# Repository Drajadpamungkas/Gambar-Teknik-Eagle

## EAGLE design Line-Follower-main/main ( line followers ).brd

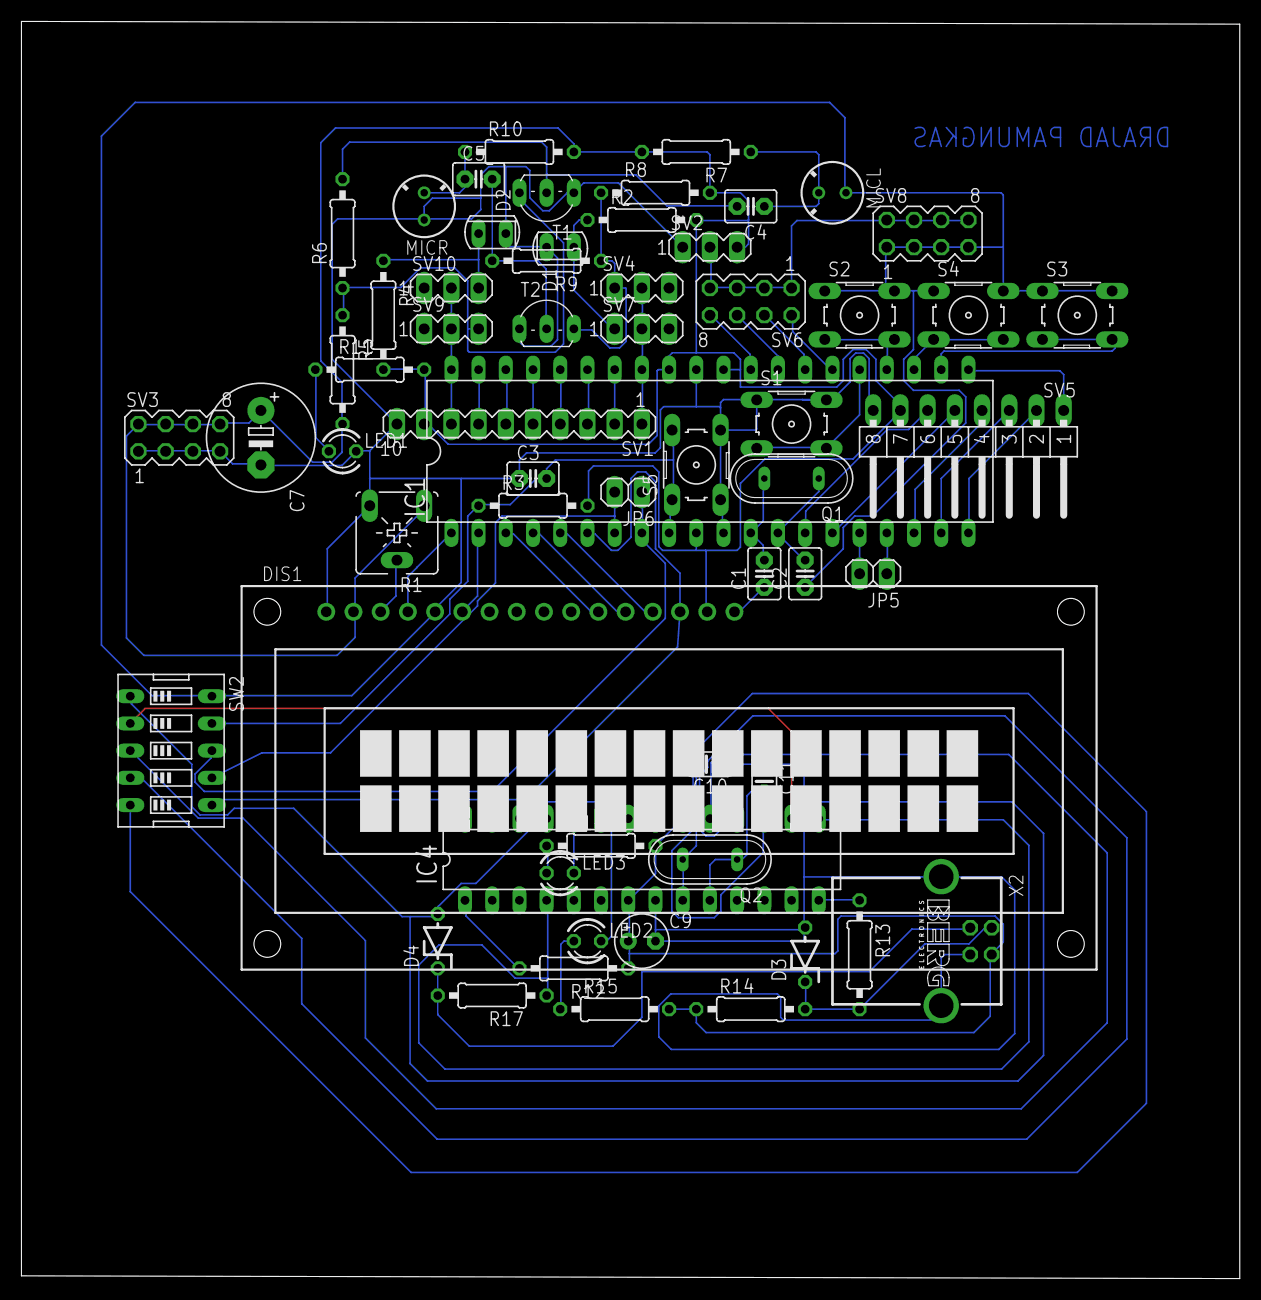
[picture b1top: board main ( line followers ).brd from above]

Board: 2 copper layers, 113.7 x 117.3 mm, 61 parts (0 on the bottom side), 65 nets.

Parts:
C1, C2: 22p; C2.5-3
C3: 10nF; C2.5-3
C4, C5: 100nF; C2.5-3
C7: 1000uF/16V; E5-10,5
C9: 10uF/16V; E2,5-5
C10, C11: 22pF; C025-024X044
D1, D2: SFH225
D3, D4: DZ3,6V; ZDIO-5
DIS1: TUXGR_16X2_R2
IC1: MEGA16-P; DIL40
IC4: MEGA8-P; DIL28-3
JP5, JP6: 1X02
LED1: merah; LED3MM
LED2: Merah; LED3MM
LED3: hijau; LED3MM
MICL: MC; F6050AP
MICR: MC; F6050AP
Q1: 8MHz; QS
Q2: 12MHz; QS
R1: 20K; CA6V
R2, R4: 56K; 0207/10
R3, R5, R7, R8, R10, R12: 10K; 0207/10
R6, R9: 100K; 0207/10
R11, R15, R16: 330; 0207/10
R13, R17: 68; 0207/10
R14: 2K2; 0207/10
S1, S2, S3, S4, S5: B3F-10XX
SV1: MA10-1
SV2, SV4, SV7, SV9, SV10: MA03-1
SV3, SV6, SV8: MA04-2
SV5: MA08-1W
SW2: EDG-05
T1, T2: TO92-EBC
X2: PN61729-S

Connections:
DGND: C9.-, C10.1, C11.1, D3.A, D4.A, IC4.8, IC4.22, SW2.1, X2.4, X2.S1, X2.S2
GND: C1.1, C2.1, C3.1, C7.-, D1.K, D2.K, DIS1.1, DIS1.5, DIS1.16, IC1.11, IC1.31, LED1.K, MICL.1, MICR.1, R1.E, S1.1, S1.2, S2.1, S2.2, S3.1, S3.2, S4.1, S4.2, S5.3, S5.4, SV1.10, SV2.1, SV3.1, SV3.3, SV3.5, SV3.7, SV5.8, SV8.1, SV8.3, SV8.5, SV8.7, SW2.10, T1.E, T2.E
MISO: IC1.7, JP6.2, SW2.7
MOSI: DIS1.14, IC1.6, SW2.6
unnamed: IC1.33, SV1.1, SV4.2, SV7.2
unnamed: IC1.34, SV1.2
unnamed: IC1.35, SV1.3
unnamed: IC1.36, SV1.4
unnamed: IC1.37, SV1.5
unnamed: IC1.38, SV1.6
unnamed: IC1.39, SV1.7
unnamed: D2.A, R4.1, SV10.3
unnamed: IC1.24, S2.3, S2.4
unnamed: DIS1.13, IC1.5
unnamed: DIS1.12, IC1.4
unnamed: DIS1.11, IC1.3
unnamed: DIS1.6, IC1.2
unnamed: R5.1, R6.1, SV9.3, T1.C
unnamed: DIS1.3, R1.S
unnamed: C1.2, IC1.12, Q1.2
unnamed: C2.2, IC1.13, Q1.1
unnamed: DIS1.4, IC1.1
unnamed: D1.A, R2.1, SV7.1
unnamed: IC1.23, S4.3, S4.4
unnamed: IC1.40, SV1.8, SV9.2, SV10.2
unnamed: C4.2, R6.2, T1.B
unnamed: C4.1, MICL.2, R7.1
unnamed: R8.1, R9.1, SV4.1, T2.C
unnamed: C5.2, R9.2, T2.B
unnamed: C5.1, MICR.2, R10.1
unnamed: IC1.22, S3.3, S3.4
unnamed: IC1.25, S1.3, S1.4
unnamed: IC1.21, SV5.1
unnamed: IC1.20, SV5.2
unnamed: IC1.19, SV5.3
unnamed: IC1.18, SV5.4
unnamed: IC1.15, SV5.5
unnamed: IC1.14, SV5.6
unnamed: IC1.16, JP5.2
unnamed: IC1.17, JP5.1
unnamed: LED1.A, R11.1
unnamed: IC4.1, R12.2
unnamed: IC1.26, SV6.2
unnamed: IC1.27, SV6.4
unnamed: IC1.28, SV6.6
unnamed: IC1.29, SV6.8
unnamed: C10.2, IC4.9, Q2.2
unnamed: C11.2, IC4.10, Q2.1
unnamed: IC4.14, R13.1
unnamed: LED2.A, R15.1
unnamed: LED3.A, R16.1
unnamed: IC4.23, LED2.K
unnamed: IC4.24, LED3.K
unnamed: D4.C, R17.2, X2.3
unnamed: IC4.4, IC4.15, R17.1
unnamed: D3.C, R13.2, R14.2, X2.2
unnamed: IC4.17, SW2.5
unnamed: IC4.18, SW2.4
unnamed: IC4.19, SW2.3
unnamed: IC4.16, SW2.2
RESET: C3.2, IC1.9, R3.1, S5.1, S5.2, SW2.9
SCK: IC1.8, JP6.1, SW2.8
VCC: C7.+, DIS1.2, DIS1.15, IC1.10, IC1.30, IC1.32, R1.A, R2.2, R3.2, R4.2, R5.2, R7.2, R8.2, R10.2, R11.2, SV1.9, SV2.3, SV3.2, SV3.4, SV3.6, SV3.8, SV5.7
VDD: SV2.2, SV6.1, SV6.3, SV6.5, SV6.7, SV8.2, SV8.4, SV8.6, SV8.8
VPP: C9.+, IC4.7, IC4.20, R12.1, R14.1, R15.2, R16.2, X2.1

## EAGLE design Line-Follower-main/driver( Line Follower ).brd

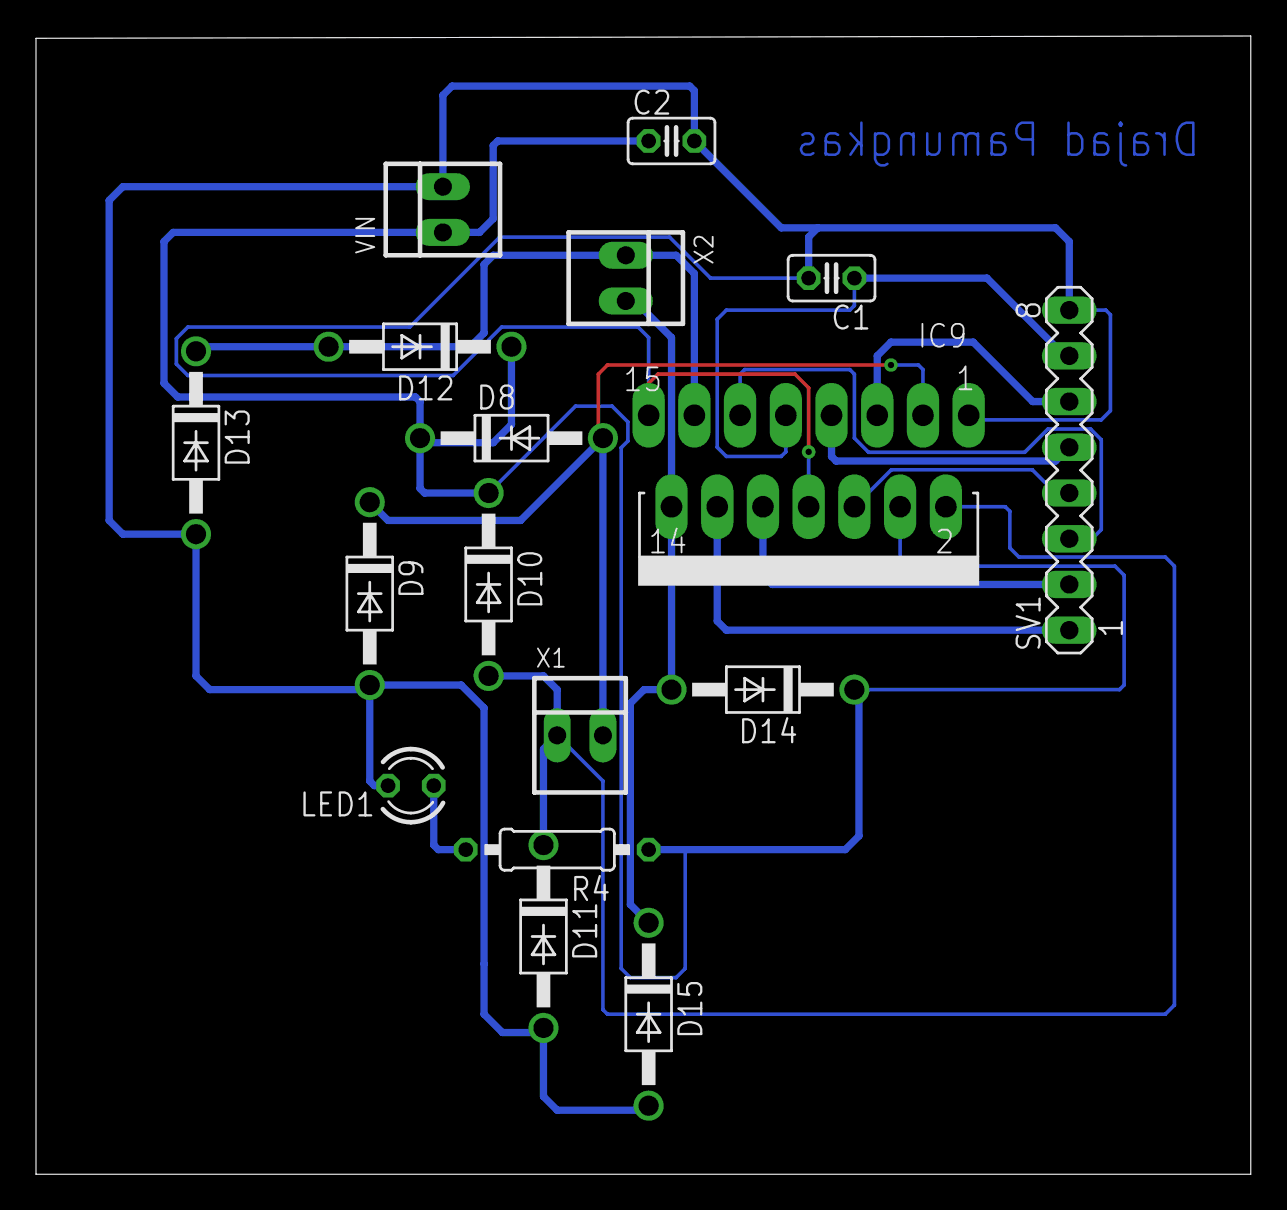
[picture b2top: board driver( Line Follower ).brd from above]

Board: 2 copper layers, 67.5 x 63.2 mm, 17 parts (0 on the bottom side), 14 nets.

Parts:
C1, C2: 100nF; C025-025X050
D8, D9, D10, D11, D12, D13, D14, D15: 1N4004; DO41-10
IC9: L298; MULTIWATT-15
LED1: LED3MM
R4: 330; 0207/10
SV1: MA08-1
VIN: 22-23-2021
X1, X2: 22-23-2021

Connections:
GND: C1.2, C2.2, D9.A, D11.A, D13.A, D15.A, IC9.1, IC9.8, IC9.15, LED1.K, SV1.8, VIN.2
unnamed: IC9.5, SV1.6
unnamed: IC9.7, SV1.5
unnamed: IC9.12, SV1.1
unnamed: IC9.10, SV1.2
unnamed: IC9.6, SV1.4
unnamed: IC9.11, SV1.3
unnamed: LED1.A, R4.2
unnamed: D8.A, D9.C, IC9.3, X1.2
unnamed: D10.A, D11.C, IC9.2, X1.1
unnamed: D12.A, D13.C, IC9.13, X2.1
unnamed: D14.A, D15.C, IC9.14, X2.2
VCC: C1.1, IC9.9, SV1.7
VDD: C2.1, D8.C, D10.C, D12.C, D14.C, IC9.4, R4.1, VIN.1

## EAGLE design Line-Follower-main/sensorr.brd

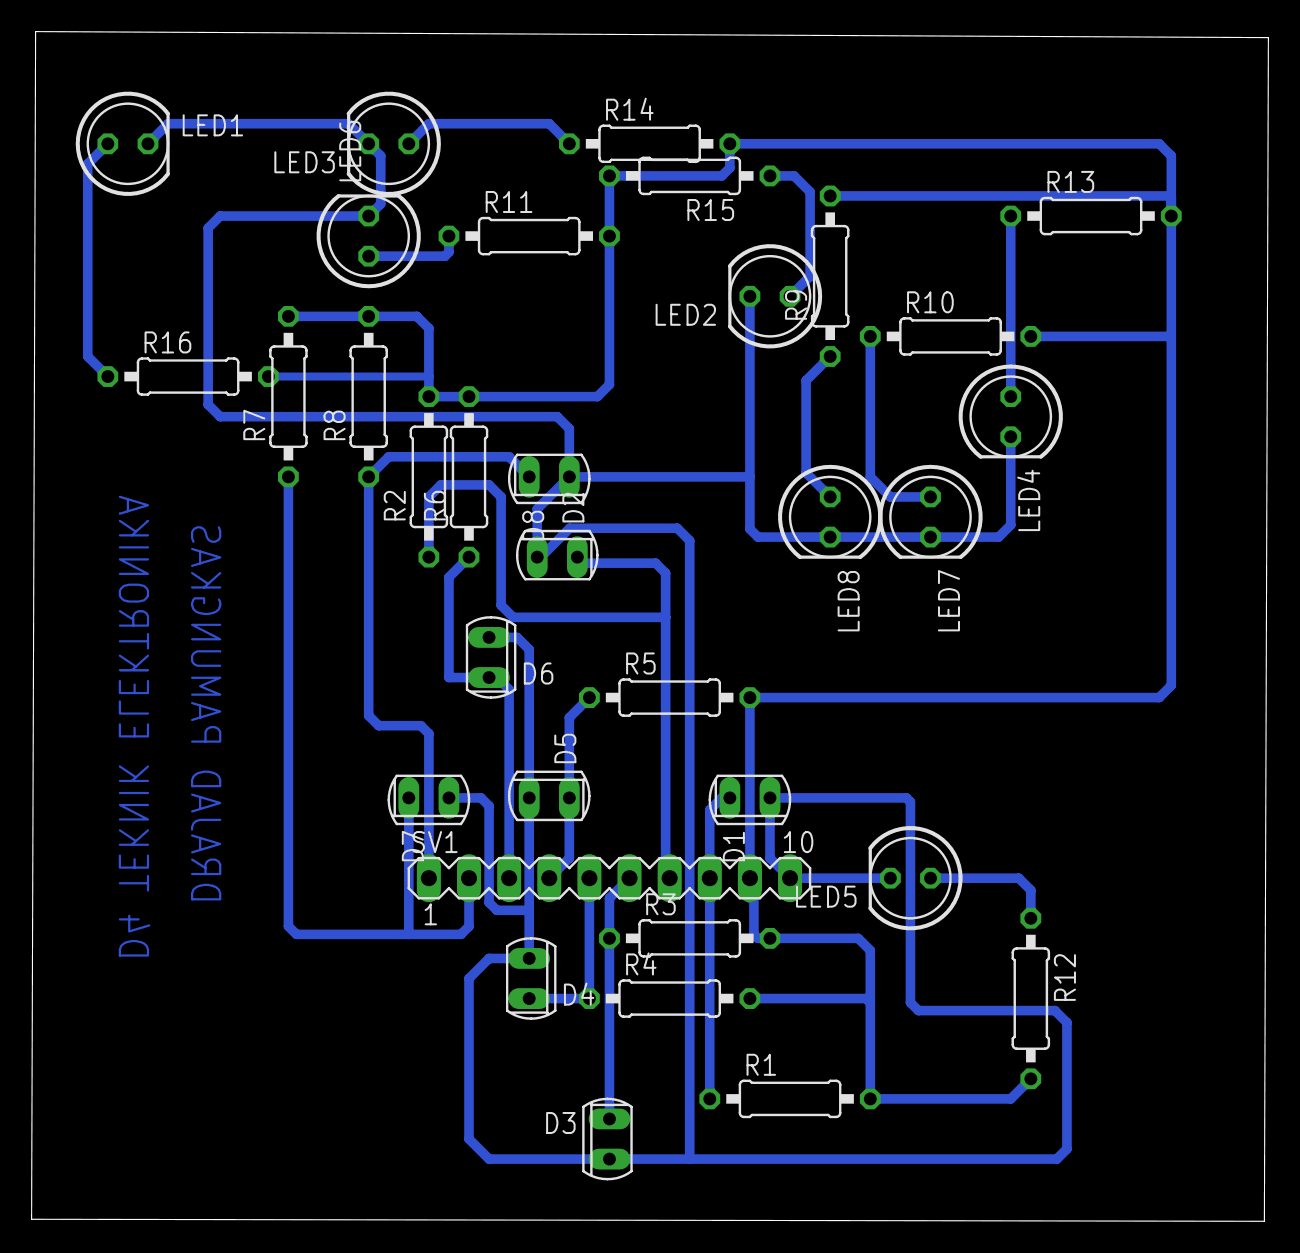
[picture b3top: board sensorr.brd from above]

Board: 2 copper layers, 78.3 x 75.3 mm, 33 parts (0 on the bottom side), 18 nets.

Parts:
D1, D2, D3, D4, D5, D6, D7, D8: PhotoDioda; SFH225
LED1, LED2, LED3, LED4, LED5, LED6, LED7, LED8: LED putih SB; LED5MM
R1, R2, R3, R4, R5, R6, R7, R8: 0207/10
R9, R10, R11, R12, R13, R14, R15, R16: 330; 0207/10
SV1: MA10-1

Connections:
GND: D1.A, D2.A, D3.A, D4.A, D5.A, D6.A, D7.A, D8.A, LED1.K, LED2.K, LED3.K, LED4.K, LED5.K, LED6.K, LED7.K, LED8.K, SV1.10
unnamed: LED7.A, R10.1
unnamed: D7.K, R7.1, SV1.2
unnamed: D8.K, R8.1, SV1.1
unnamed: D1.K, R1.1, SV1.8
unnamed: D2.K, R2.1, SV1.7
unnamed: D3.K, R3.1, SV1.6
unnamed: D5.K, R5.1, SV1.4
unnamed: D4.K, R4.1, SV1.5
unnamed: D6.K, R6.1, SV1.3
unnamed: LED6.A, R11.1
unnamed: LED5.A, R12.1
unnamed: LED4.A, R13.1
unnamed: LED3.A, R14.1
unnamed: LED2.A, R15.1
unnamed: LED1.A, R16.1
unnamed: LED8.A, R9.1
VCC: R1.2, R2.2, R3.2, R4.2, R5.2, R6.2, R7.2, R8.2, R9.2, R10.2, R11.2, R12.2, R13.2, R14.2, R15.2, R16.2, SV1.9

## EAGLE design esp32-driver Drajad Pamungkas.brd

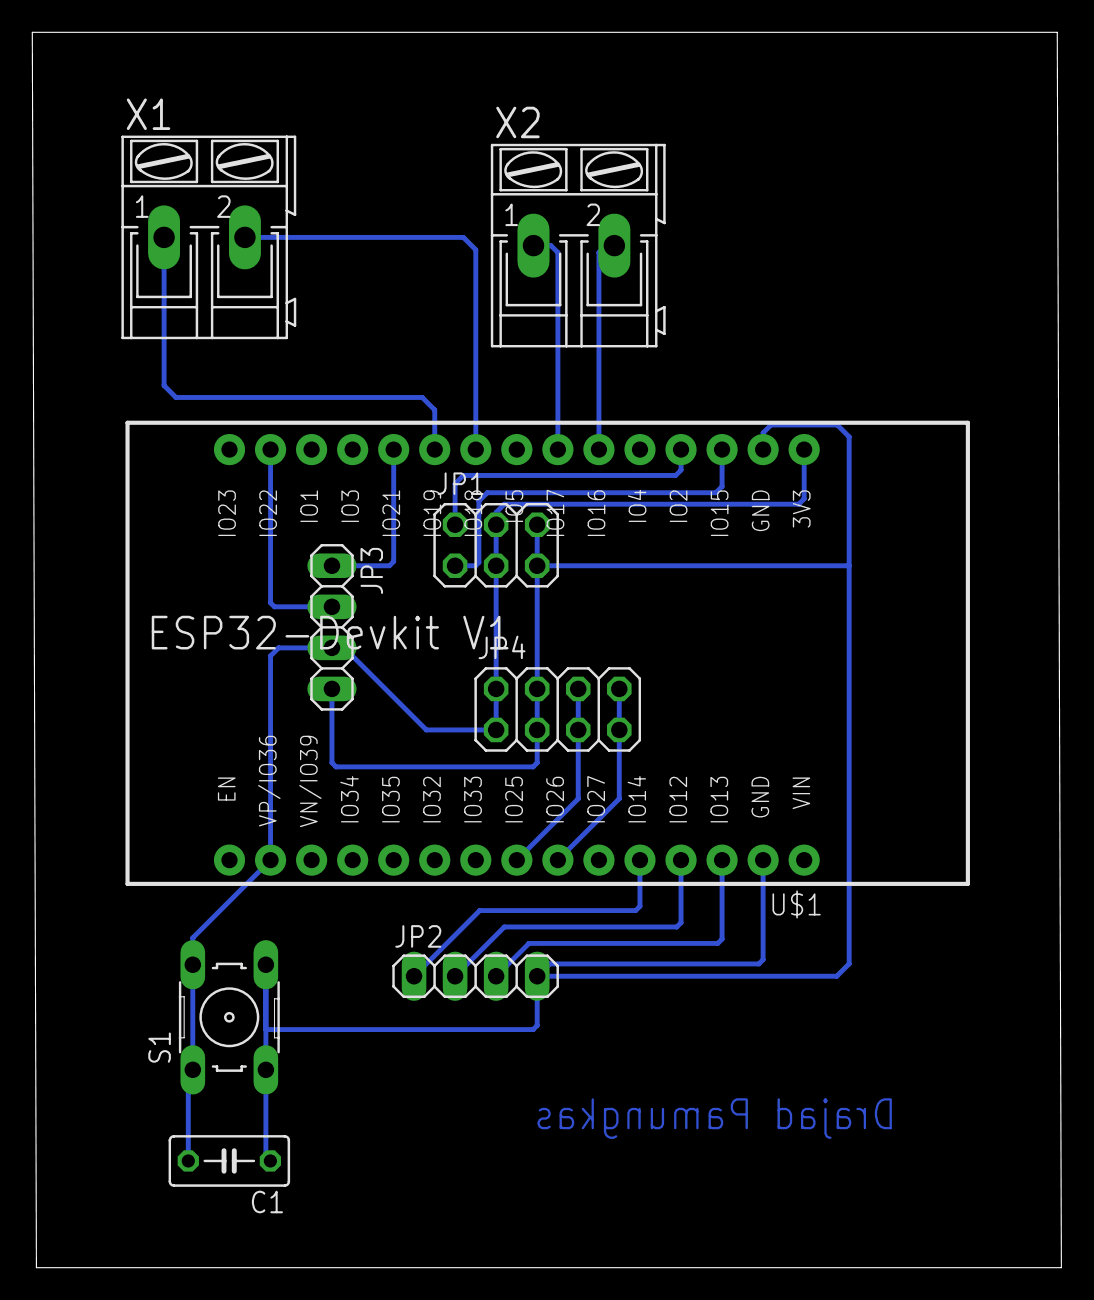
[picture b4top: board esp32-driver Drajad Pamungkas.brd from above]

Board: 2 copper layers, 63.7 x 76.4 mm, 9 parts (0 on the bottom side), 15 nets.

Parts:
C1: C050-030X075
JP1: 2X03
JP2, JP3: 1X04
JP4: 2X04
S1: B3F-10XX
U$1: ESP32DEVKITV1; ESP32-DEVKITV1
X1, X2: AK300/2

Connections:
GND: C1.1, JP1.5, JP1.6, JP2.4, JP3.4, JP4.3, JP4.4, S1.3, S1.4, U$1.GND@1, U$1.GND@2
MOISTURE: JP1.2, U$1.D2
unnamed: U$1.D19, X1.1
unnamed: U$1.D18, X1.2
unnamed: U$1.D17, X2.1
unnamed: U$1.D16, X2.2
OUT1: JP2.1, U$1.D14
OUT2: JP2.2, U$1.D12
OUT3: JP2.3, U$1.D13
PH: JP1.1, U$1.D15
SCL: JP3.2, U$1.D22
SCL2: JP4.5, JP4.6, U$1.D25
SDA: JP3.1, U$1.D21
SDA2: JP4.7, JP4.8, U$1.D26
V: C1.2, JP1.3, JP1.4, JP3.3, JP4.1, JP4.2, S1.1, S1.2, U$1.3V3, U$1.D36

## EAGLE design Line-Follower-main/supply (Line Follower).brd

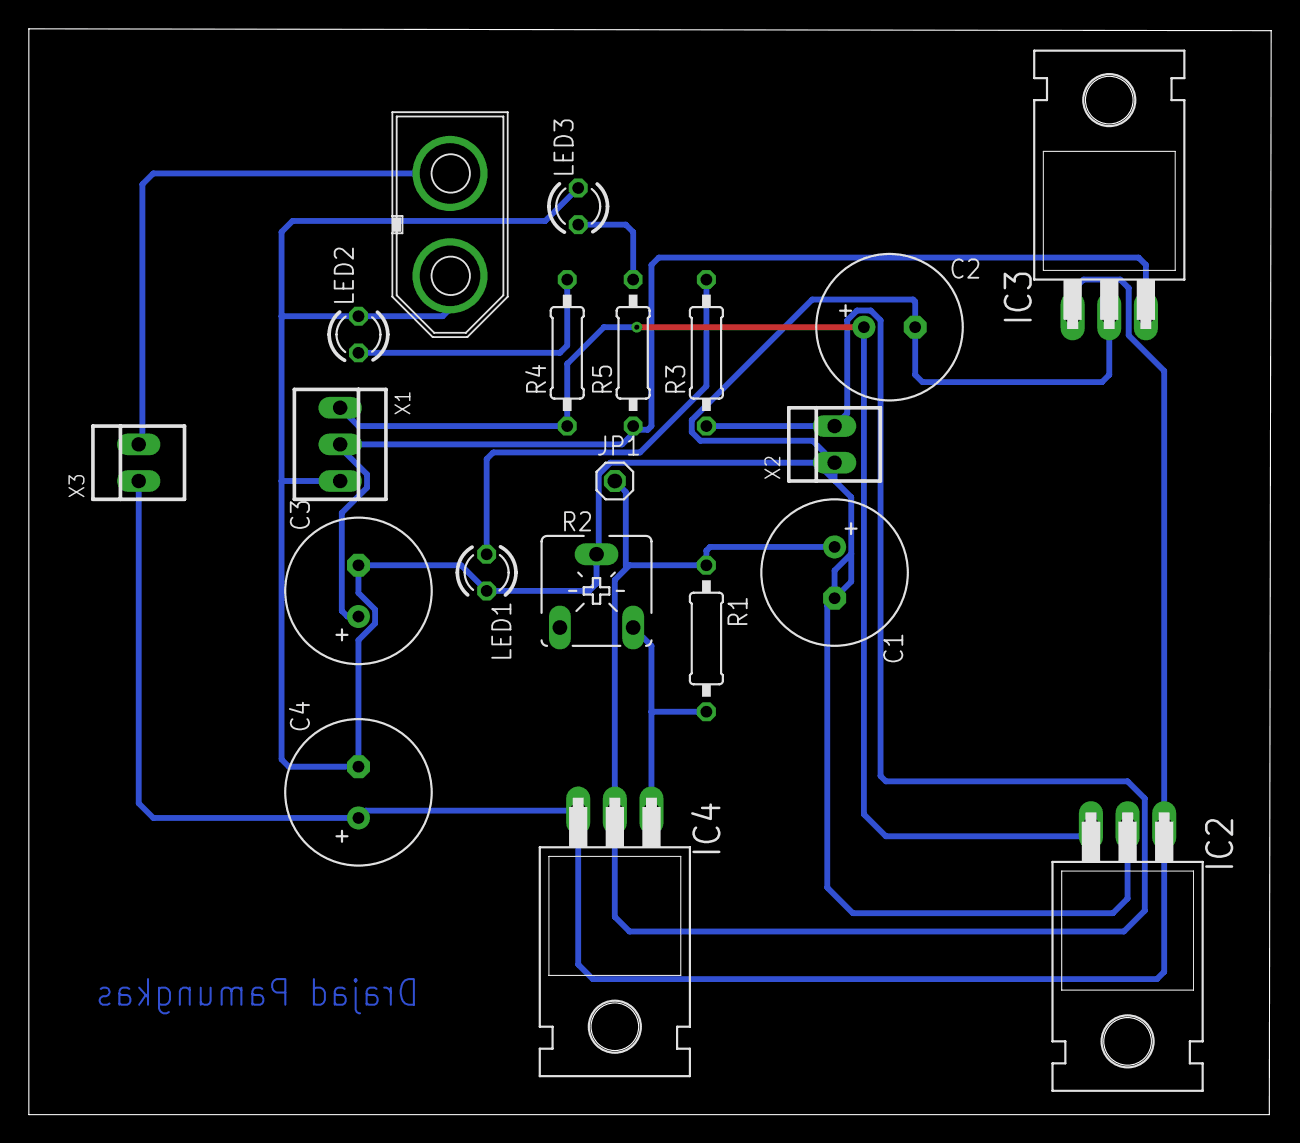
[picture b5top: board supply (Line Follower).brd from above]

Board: 2 copper layers, 86.2 x 75.3 mm, 20 parts (0 on the bottom side), 10 nets.

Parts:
C1, C2, C3, C4: 1000uF/16V; E3,5-10
IC2, IC3: 7805T; TO220H
IC4: 317T; TO220H
JP1: 1X01
LED1, LED2, LED3: LED3MM
R1: 1K2; 0207/10
R2: 20K; CA6V
R3, R4, R5: 1K; 0207/10
VIN: CON-XT60M
X1: VSYS; 22-23-2031
X2: VMOT; 22-23-2021
X3: switch; 22-23-2021

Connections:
+12V: C3.+, IC3.3, R5.1, X1.2
GND: C1.-, C2.-, C3.-, C4.-, IC2.2, IC3.2, LED1.K, LED2.K, LED3.K, R2.S, VIN.V-, X1.3, X2.1
unnamed: IC4.1, R1.2, R2.E
unnamed: LED1.A, R3.2
unnamed: LED3.A, R5.2
unnamed: VIN.V+, X3.2
unnamed: LED2.A, R4.2
VCC: C2.+, IC2.3, R4.1, X1.1
VDD: C1.+, IC4.2, JP1.1, R1.1, R3.1, X2.2
VPP: C4.+, IC2.1, IC3.1, IC4.3, X3.1

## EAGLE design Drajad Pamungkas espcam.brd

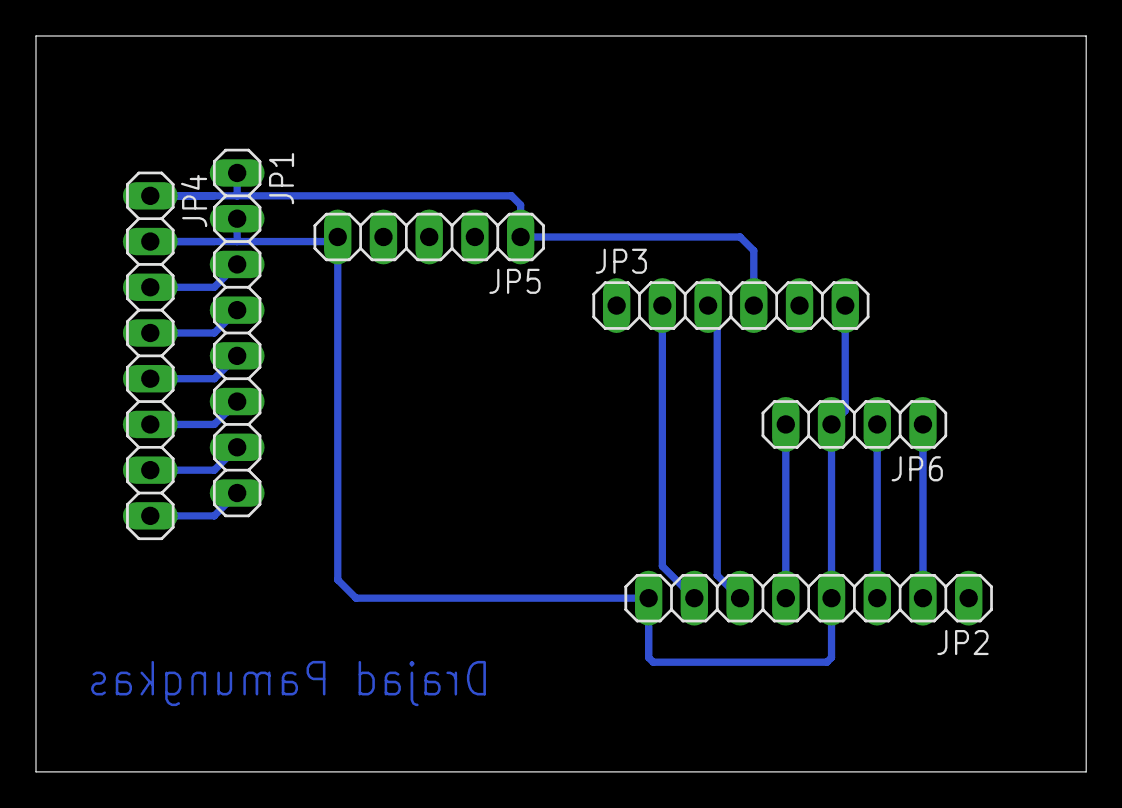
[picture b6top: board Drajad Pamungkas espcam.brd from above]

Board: 2 copper layers, 58.3 x 40.9 mm, 6 parts (0 on the bottom side), 13 nets.

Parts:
JP1, JP2, JP4: 1X08
JP3: 1X06
JP5: 1X05
JP6: 1X04

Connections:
5V: JP1.1, JP3.4, JP4.1, JP5.1
GND: JP1.2, JP2.4, JP2.8, JP3.6, JP4.2, JP5.5, JP6.3
IO0: JP2.3, JP6.2
IO2: JP1.7, JP4.7
IO4: JP1.8, JP4.8
IO12: JP1.3, JP4.3
IO13: JP1.4, JP4.4
IO14: JP1.6, JP4.6
IO15: JP1.5, JP4.5
IO16: JP2.2, JP6.1
RX: JP2.7, JP3.2
TX: JP2.6, JP3.3
VOUT: JP2.5, JP6.4

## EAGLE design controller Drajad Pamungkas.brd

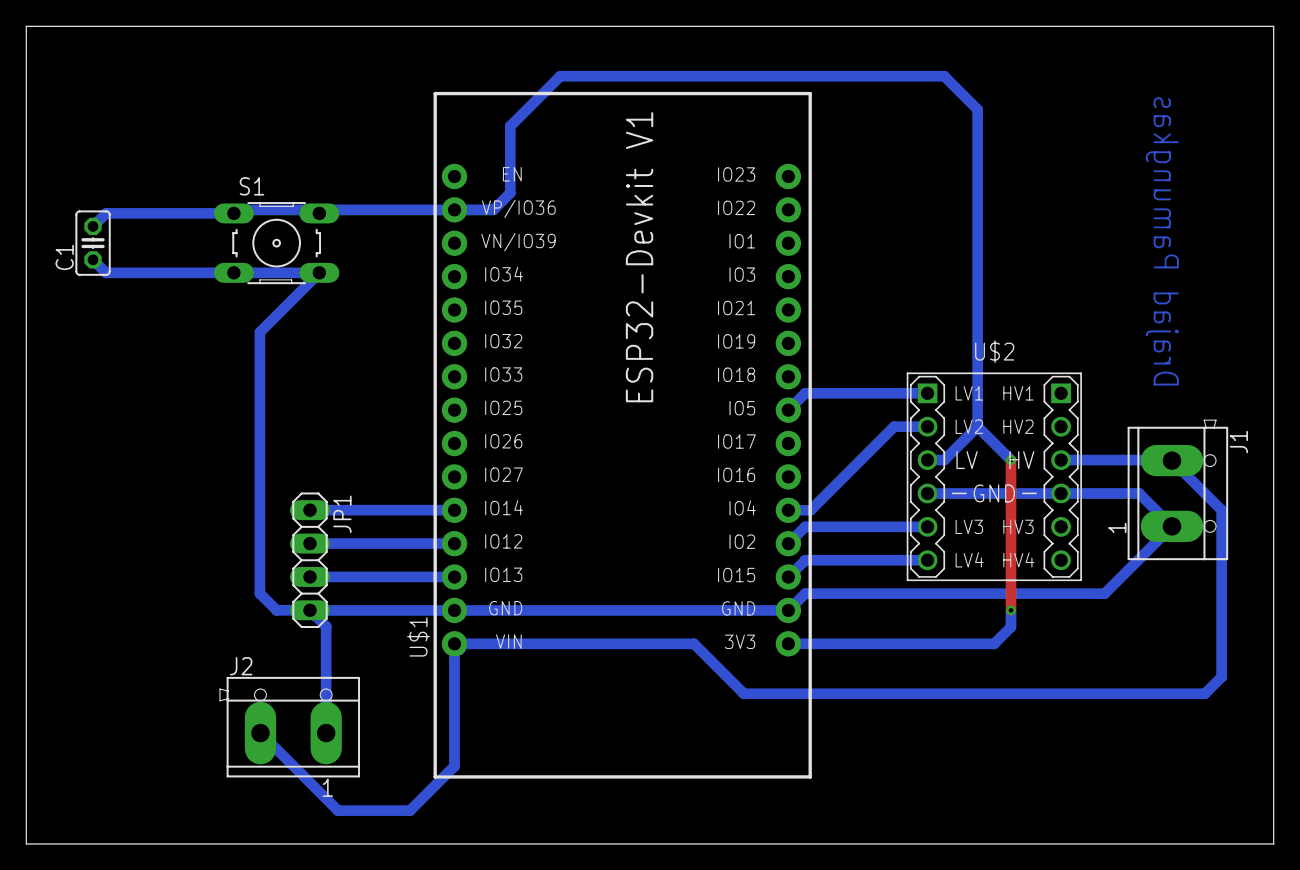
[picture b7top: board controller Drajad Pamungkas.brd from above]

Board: 2 copper layers, 94.9 x 62.2 mm, 7 parts (0 on the bottom side), 10 nets.

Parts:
C1: C025-025X050
J1, J2: CON_TERMINAL_BLOCK_02-5MM; TERMINAL_BLOCK_2P_5
JP1: 1X04
S1: B3F-10XX
U$1: ESP32DEVKITV1; ESP32-DEVKITV1
U$2: LEVEL-SHIFTER-4CH

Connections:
GND: C1.1, J1.1, J2.1, JP1.4, S1.3, S1.4, U$1.GND@1, U$1.GND@2, U$2.J1.4, U$2.J2.4
HV: J1.2, J2.2, U$1.VIN, U$2.J2.3
LV: C1.2, S1.1, S1.2, U$1.3V3, U$1.D36, U$2.J1.3
LV1: U$1.D5, U$2.J1.1
LV2: U$1.D4, U$2.J1.2
LV3: U$1.D2, U$2.J1.5
LV4: U$1.D15, U$2.J1.6
OUT1: JP1.1, U$1.D14
OUT2: JP1.2, U$1.D12
OUT3: JP1.3, U$1.D13

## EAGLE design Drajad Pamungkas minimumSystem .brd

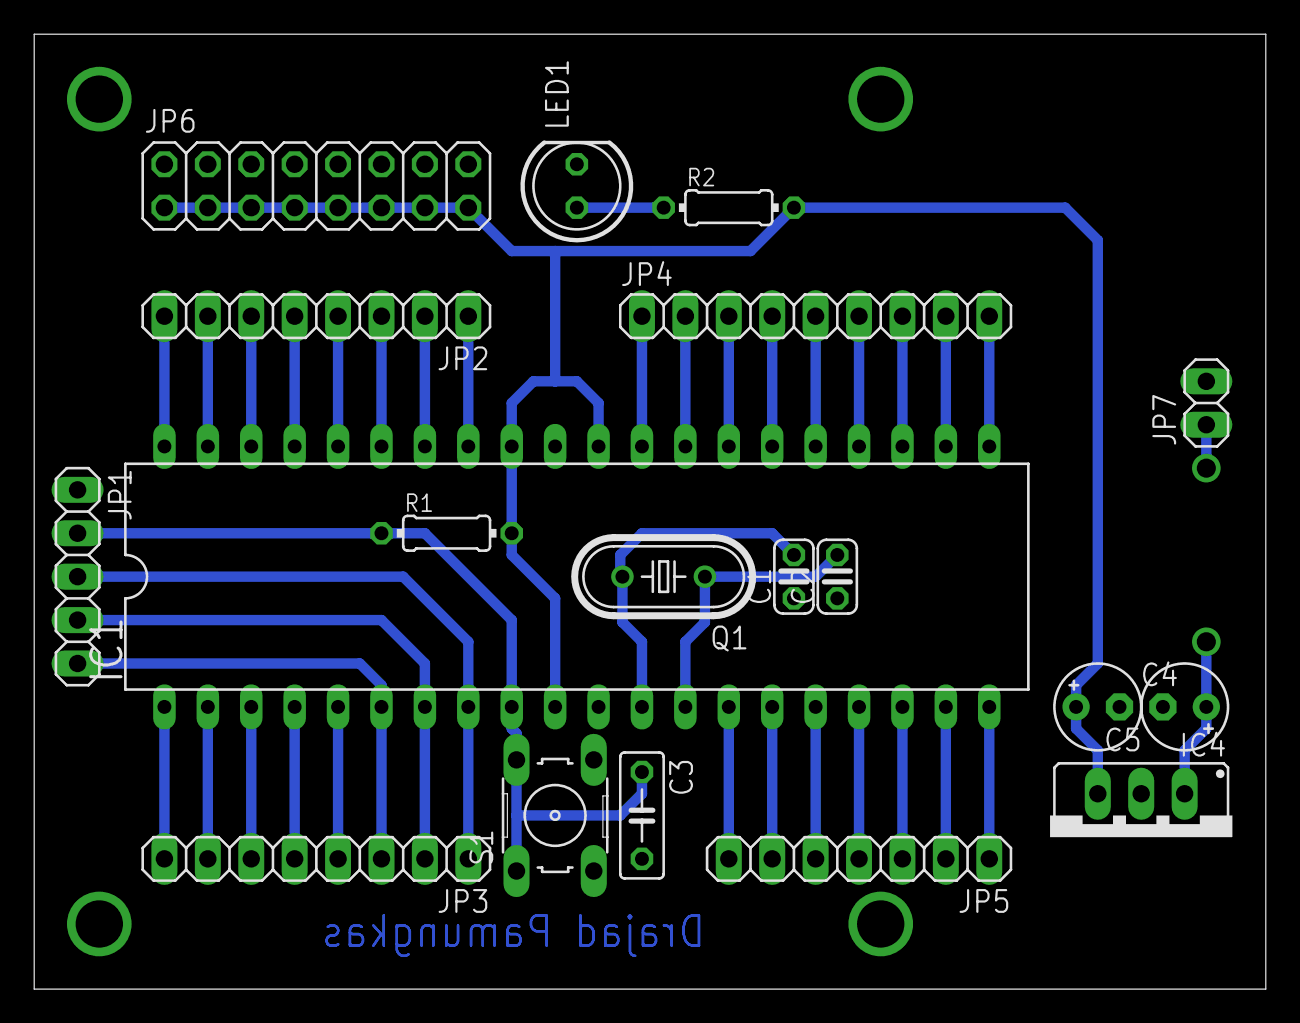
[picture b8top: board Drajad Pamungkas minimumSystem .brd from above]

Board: 2 copper layers, 72.1 x 55.9 mm, 20 parts (1 on the bottom side), 40 nets.

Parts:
C1, C2: C025-024X044
C3: C050-025X075
C4, C5: E2,5-5
D1: 1N4004; DO41-10
IC1: MEGA16-P; DIL40
IC4: 78XXS
JP1: 1X05
JP2, JP3: 1X08
JP4: 1X09
JP5: 1X07
JP6: 2X08
JP7: 1X02
LED1: LED5MM
Q1: HC49U-V
R1, R2: 0204/7
S1: B3F-10XX

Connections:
+5V: C4.+, IC1.10, IC1.30, IC1.32, IC4.OUT, JP6.1, JP6.3, JP6.5, JP6.7, JP6.9, JP6.11, JP6.13, JP6.15, R1.2, R2.2
+12V: D1.A, JP7.1
C0: IC1.22, JP4.8
C1: IC1.23, JP4.7
C2: IC1.24, JP4.6
C3: IC1.25, JP4.5
D7: IC1.14, JP5.7
GND: C1.1, C2.1, C3.2, C4.-, C5.-, IC1.11, IC1.31, IC4.GND, JP1.1, JP6.2, JP6.4, JP6.6, JP6.8, JP6.10, JP6.12, JP6.14, JP6.16, JP7.2, LED1.K, S1.3, S1.4
unnamed: IC1.33, JP2.1
unnamed: IC1.34, JP2.2
unnamed: IC1.35, JP2.3
unnamed: IC1.36, JP2.4
unnamed: IC1.37, JP2.5
unnamed: IC1.38, JP2.6
unnamed: IC1.39, JP2.7
unnamed: IC1.40, JP2.8
unnamed: IC1.29, JP4.1
unnamed: IC1.28, JP4.2
unnamed: IC1.27, JP4.3
unnamed: IC1.5, JP3.4
unnamed: IC1.20, JP5.1
unnamed: IC1.19, JP5.2
unnamed: IC1.26, JP4.4
unnamed: IC1.6, JP1.5, JP3.3
unnamed: IC1.4, JP3.5
unnamed: IC1.3, JP3.6
unnamed: IC1.2, JP3.7
unnamed: IC1.1, JP3.8
unnamed: C5.+, D1.C, IC4.IN
unnamed: IC1.15, JP5.6
unnamed: IC1.16, JP5.5
unnamed: IC1.17, JP5.4
unnamed: C3.1, IC1.9, JP1.2, R1.1, S1.1, S1.2
unnamed: IC1.18, JP5.3
unnamed: C1.2, IC1.12, Q1.2
unnamed: C2.2, IC1.13, Q1.1
unnamed: LED1.A, R2.1
unnamed: IC1.8, JP1.3, JP3.1
unnamed: IC1.7, JP1.4, JP3.2
RS: IC1.21, JP4.9

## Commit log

2021-11-18 Create Line Follower
2024-07-17 menambahkan file

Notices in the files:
parts and their libraries:
diy-model: Released under the Creative Commons Attribution 4.0 International License: http://creativecommons.org/licenses/by/4.0
